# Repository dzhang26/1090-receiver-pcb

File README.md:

# 1090-receiver-pcb
PCB design for the 1.09 GHz mode-A/C/S / ADS-B receiver

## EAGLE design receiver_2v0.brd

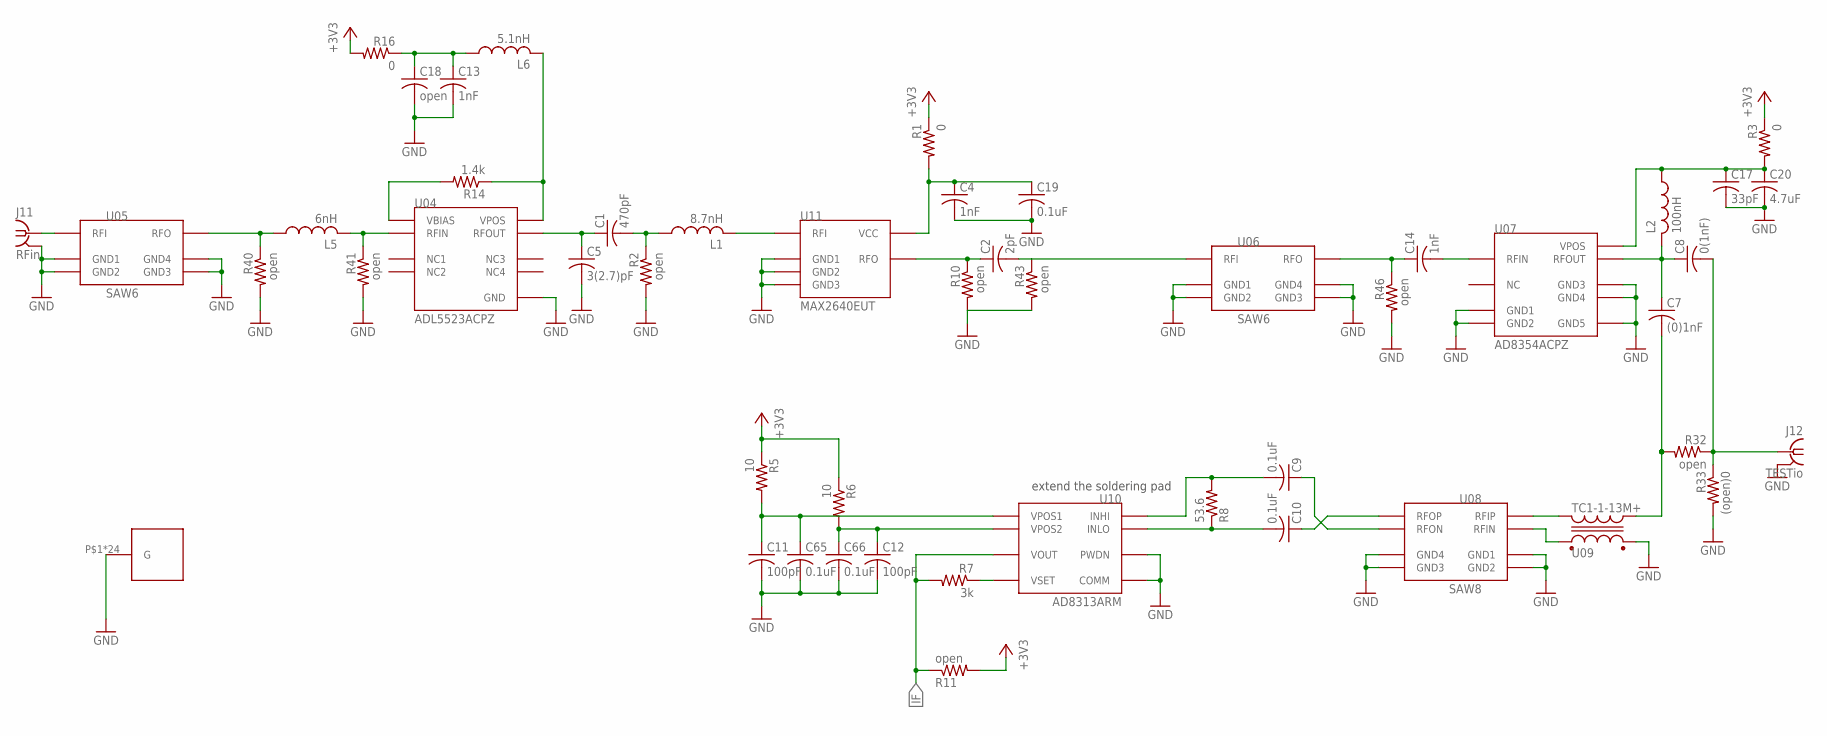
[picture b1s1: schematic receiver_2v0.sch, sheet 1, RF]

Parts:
C1: 470pF; C0603
C2: 2pF; C0603
C4, C13, C14: 1nF; C0603
C5: 3(2.7)pF; C0603
C7: (0)1nF; C0603
C8: 0(1nF); C0603
C9, C10, C19, C65, C66: 0.1uF; C0603
C11, C12: 100pF; C0603
C17: 33pF; C0603
C18: open; C0603
C20: 4.7uF; C0603
J11: RFin; J502-ND-142-0711-821/826; MPN 142-0711-821
J12: TESTio; J502-ND-142-0711-821/826; MPN 142-0711-821
L1: 8.7nH; L0603
L2: 100nH; L0603
L5: 6nH; L0603
L6: 5.1nH; L0603
R1, R3, R16: 0; R0603
R2, R10, R11, R32, R40, R41, R43, R46: open; R0603
R5, R6: 10; R0603
R7: 3k; R0603
R8: 53.6; R0603
R14: 1.4k; R0603
R33: (open)0; R0603
U04: ADL5523ACPZ; CP-8-2
U05, U06: SAW6
U07: AD8354ACPZ; CP-8-1
U08: SAW8
U09: TC1-1-13M+; AT224-1A
U10: AD8313ARM; RM-08
U11: MAX2640EUT; SOT23-6
U$8: BMI-S-5; BMI-S-105

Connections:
+3V3: R1.1, R3.1, R5.1, R6.1, R11.2, R16.2; also elsewhere on the board
GND: C4.2, C5.2, C11.2, C12.2, C13.2, C17.2, C18.2, C19.2, C20.2, C65.2, C66.2, J11.G@1 (GND), J11.G@2 (GND), J11.G@3 (GND), J11.G@4 (GND), J12.G@1 (GND), J12.G@2 (GND), J12.G@3 (GND), J12.G@4 (GND), R2.2, R10.2, R33.2, R40.2, R41.2, R43.2, R46.2, U04.9 (GND), U05.A (GND1), U05.C (GND2), U05.D (GND3), U05.F (GND4), U06.A (GND1), U06.C (GND2), U06.D (GND3), U06.F (GND4), U07.1 (GND1), U07.4 (GND2), U07.5 (GND3), U07.8 (GND4), U07.9 (GND5), U08.P3 (GND1), U08.P4 (GND2), U08.P7 (GND3), U08.P8 (GND4), U09.1 (SD), U10.5 (PWDN), U10.6 (COMM), U11.2 (GND1), U11.3 (GND2), U11.5 (GND3), U$8.P$1, U$8.P$2, U$8.P$3, U$8.P$4, U$8.P$5, U$8.P$6, U$8.P$7, U$8.P$8, U$8.P$9, U$8.P$10, U$8.P$11, U$8.P$12, U$8.P$13, U$8.P$15, U$8.P$16, U$8.P$17, U$8.P$18, U$8.P$20, U$8.P$21, U$8.P$22, U$8.P$23, U$8.P$24, U$8.P$25, U$8.P$26; also elsewhere on the board
IF: R7.2, R11.1, U10.8 (VOUT); also elsewhere on the board
unnamed: L1.2, U11.1 (RFI)
unnamed: C1.1, C5.1, U04.7 (RFOUT)
unnamed: C2.1, R10.1, U11.4 (RFO)
unnamed: C13.1, C18.1, L6.1, R16.1
unnamed: C14.2, U07.3 (RFIN)
unnamed: J11.1, U05.B (RFI)
unnamed: L6.2, R14.1, U04.8 (VPOS)
unnamed: C4.1, C19.1, R1.2, U11.6 (VCC)
unnamed: C17.1, C20.1, L2.1, R3.2, U07.6 (VPOS)
unnamed: C10.2, R8.1, U10.3 (INLO)
unnamed: C11.1, C65.1, R5.2, U10.1 (VPOS1)
unnamed: C12.1, C66.1, R6.2, U10.4 (VPOS2)
unnamed: C10.1, U08.P5 (RFOP)
unnamed: C9.1, U08.P6 (RFON)
unnamed: C9.2, R8.2, U10.2 (INHI)
unnamed: C7.1, C8.1, L2.2, U07.7 (RFOUT)
unnamed: C8.2, J12.1, R32.1, R33.1
unnamed: U08.P1 (RFIP), U09.4
unnamed: U08.P2 (RFIN), U09.6 (PD)
unnamed: C14.1, R46.1, U06.E (RFO)
unnamed: R14.2, U04.1 (VBIAS)
unnamed: L5.1, R40.1, U05.E (RFO)
unnamed: L5.2, R41.1, U04.2 (RFIN)
unnamed: R7.1, U10.7 (VSET)
unnamed: C1.2, L1.1, R2.1
unnamed: C2.2, R43.1, U06.B (RFI)
unnamed: C7.2, R32.2, U09.3 (S)

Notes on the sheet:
extend the soldering pad

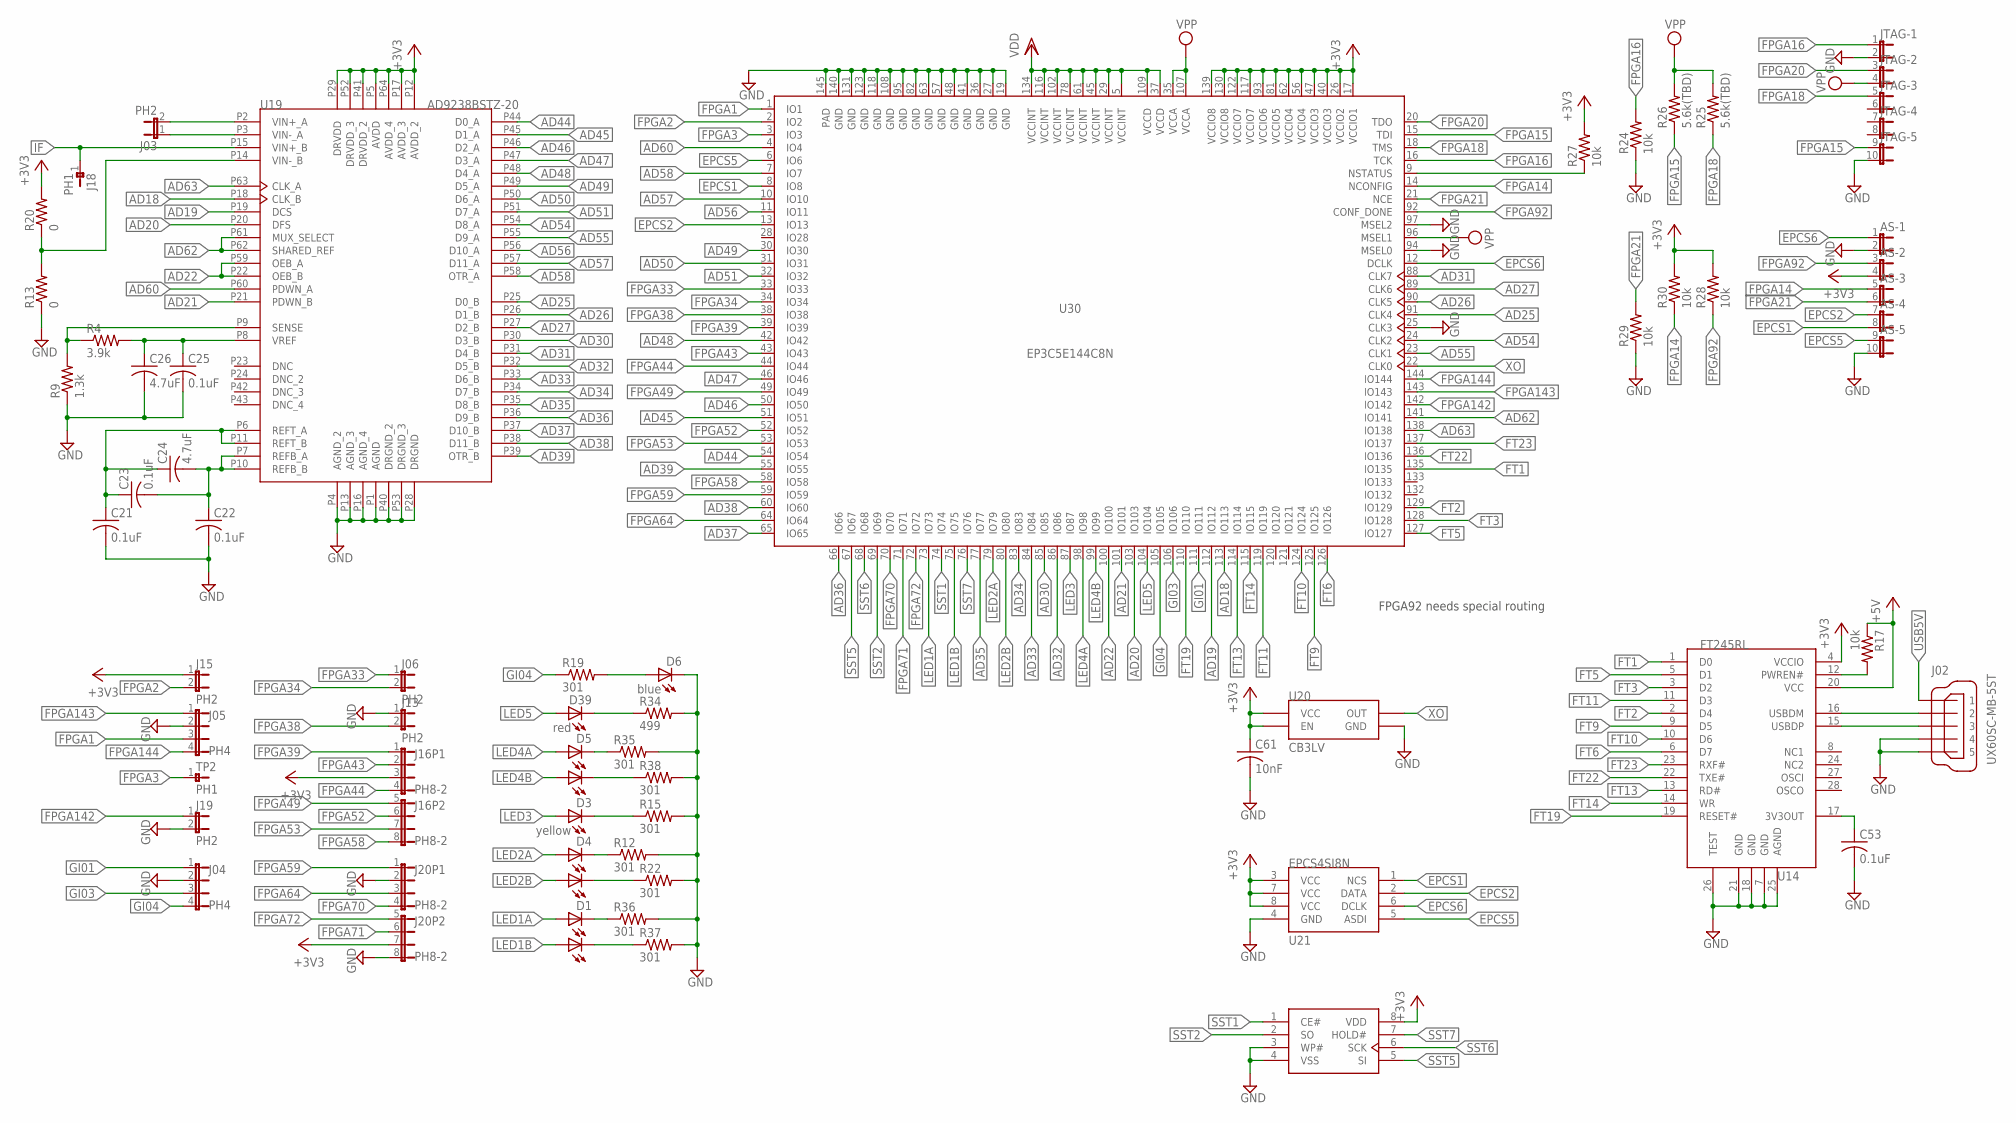
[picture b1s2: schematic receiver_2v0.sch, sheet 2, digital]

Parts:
AS: JP5QE; JP5Q
C21, C22, C23, C25, C53: 0.1uF; C0603
C24, C26: 4.7uF; C0603
C61: 10nF; C0603
D1, D4, D5: LED0606
D3: yellow; LED0603
D6: blue; LED0603
D39: red; LED0603
J02: UX60SC-MB-5ST
J03, J06, J13, J15, J19: PH2
J04, J05: PH4
J16, J20: PH8-2
J18: PH1
JTAG: JP5QE; JP5Q
R4: 3.9k; R0603
R9: 1.3k; R0603
R12, R15, R19, R22, R35, R36, R37, R38: 301; R0603
R13, R20: 0; R0603
R17, R24, R27, R28, R29, R30: 10k; R0603
R25, R26: 5.6k(TBD); R0603
R34: 499; R0603
TP2: PH1
U14: FT245RL; SSOP-28
U19: AD9238BSTZ-20; ST-64-1
U20: CB3LV; CB3
U21: EPCS4SI8N; SOIC-8
U23: SST25VF512A-33-4C-SAE; SOIC-8
U30: EP3C5E144C8N; EQFP144

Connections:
+3V3: AS.4 (2), C61.1, J15.1, J16.3, J20.7 (3), R20.2, R27.2, R28.2, R30.2, U14.4 (VCCIO), U19.P5 (AVDD), U19.P12 (AVDD_2), U19.P17 (AVDD_3), U19.P29 (DRVDD), U19.P41 (DRVDD_2), U19.P52 (DRVDD_3), U19.P64 (AVDD_4), U20.1 (EN), U20.4 (VCC), U21.3 (VCC), U21.7 (VCC), U21.8 (VCC), U23.8 (VDD), U30.17 (VCCIO1), U30.26 (VCCIO2), U30.40 (VCCIO3), U30.47 (VCCIO3), U30.56 (VCCIO4), U30.62 (VCCIO4), U30.81 (VCCIO5), U30.93 (VCCIO6), U30.117 (VCCIO7), U30.122 (VCCIO7), U30.130 (VCCIO8), U30.139 (VCCIO8); also elsewhere on the board
+5V: R17.1, U14.20 (VCC); also elsewhere on the board
AD18: U19.P18 (CLK_B), U30.113 (IO113)
AD19: U19.P19 (DCS), U30.112 (IO112)
AD20: U19.P20 (DFS), U30.103 (IO103)
AD21: U19.P21 (PDWN_B), U30.101 (IO101)
AD22: U19.P22 (OEB_B), U19.P59 (OEB_A), U30.100 (IO100)
AD25: U19.P25 (D0_B), U30.91 (CLK4)
AD26: U19.P26 (D1_B), U30.90 (CLK5)
AD27: U19.P27 (D2_B), U30.89 (CLK6)
AD30: U19.P30 (D3_B), U30.85 (IO85)
AD31: U19.P31 (D4_B), U30.88 (CLK7)
AD32: U19.P32 (D5_B), U30.86 (IO86)
AD33: U19.P33 (D6_B), U30.84 (IO84)
AD34: U19.P34 (D7_B), U30.83 (IO83)
AD35: U19.P35 (D8_B), U30.77 (IO77)
AD36: U19.P36 (D9_B), U30.66 (IO66)
AD37: U19.P37 (D10_B), U30.65 (IO65)
AD38: U19.P38 (D11_B), U30.60 (IO60)
AD39: U19.P39 (OTR_B), U30.55 (IO55)
AD44: U19.P44 (D0_A), U30.54 (IO54)
AD45: U19.P45 (D1_A), U30.51 (IO51)
AD46: U19.P46 (D2_A), U30.50 (IO50)
AD47: U19.P47 (D3_A), U30.46 (IO46)
AD48: U19.P48 (D4_A), U30.42 (IO42)
AD49: U19.P49 (D5_A), U30.30 (IO30)
AD50: U19.P50 (D6_A), U30.31 (IO31)
AD51: U19.P51 (D7_A), U30.32 (IO32)
AD54: U19.P54 (D8_A), U30.24 (CLK2)
AD55: U19.P55 (D9_A), U30.23 (CLK1)
AD56: U19.P56 (D10_A), U30.11 (IO11)
AD57: U19.P57 (D11_A), U30.10 (IO10)
AD58: U19.P58 (OTR_A), U30.7 (IO7)
AD60: U19.P60 (PDWN_A), U30.4 (IO4)
AD62: U19.P61 (MUX_SELECT), U19.P62 (SHARED_REF), U30.141 (IO141)
AD63: U19.P63 (CLK_A), U30.138 (IO138)
ADREFB: C22.1, C23.2, C24.2, U19.P7 (REFB_A), U19.P10 (REFB_B)
ADREFY: C21.1, C23.1, C24.1, U19.P6 (REFT_A), U19.P11 (REFT_B)
ADSENSE: R4.1, R9.2, U19.P9 (SENSE)
ADVINMA: J03.1, U19.P3 (VIN-_A)
ADVINMB: R13.2, R20.1, U19.P14 (VIN-_B)
ADVINPA: J03.2, U19.P2 (VIN+_A)
ADVREF: C25.1, C26.1, R4.2, U19.P8 (VREF)
EPCS1: AS.8 (2), U21.1 (NCS), U30.8 (IO8)
EPCS2: AS.7 (1), U21.2 (DATA), U30.13 (IO13)
EPCS5: AS.9 (1), U21.5 (ASDI), U30.6 (IO6)
EPCS6: AS.1, U21.6 (DCLK), U30.12 (DCLK)
FPGA1: J05.3, U30.1 (IO1)
FPGA2: J15.2, U30.2 (IO2)
FPGA3: TP2.1, U30.3 (IO3)
FPGA9: R27.1, U30.9 (NSTATUS)
FPGA14: AS.5 (1), R30.1, U30.14 (NCONFIG)
FPGA15: JTAG.9 (1), R26.1, U30.15 (TDI)
FPGA16: JTAG.1, R24.2, U30.16 (TCK)
FPGA18: JTAG.5 (1), R25.1, U30.18 (TMS)
FPGA20: JTAG.3 (1), U30.20 (TDO)
FPGA21: AS.6 (2), R29.2, U30.21 (NCE)
FPGA33: J06.1, U30.33 (IO33)
FPGA34: J06.2, U30.34 (IO34)
FPGA38: J13.2, U30.38 (IO38)
FPGA39: J16.1, U30.39 (IO39)
FPGA43: J16.2, U30.43 (IO43)
FPGA44: J16.4, U30.44 (IO44)
FPGA49: J16.5 (1), U30.49 (IO49)
FPGA52: J16.6 (2), U30.52 (IO52)
FPGA53: J16.7 (3), U30.53 (IO53)
FPGA58: J16.8 (4), U30.58 (IO58)
FPGA59: J20.1, U30.59 (IO59)
FPGA64: J20.3, U30.64 (IO64)
FPGA70: J20.4, U30.70 (IO70)
FPGA71: J20.6 (2), U30.71 (IO71)
FPGA72: J20.5 (1), U30.72 (IO72)
FPGA92: AS.3 (1), R28.1, U30.92 (CONF_DONE)
FPGA142: J19.1, U30.142 (IO142)
FPGA143: J05.1, U30.143 (IO143)
FPGA144: J05.4, U30.144 (IO144)
FT1: U14.1 (D0), U30.135 (IO135)
FT2: U14.2 (D4), U30.129 (IO129)
FT3: U14.3 (D2), U30.128 (IO128)
FT5: U14.5 (D1), U30.127 (IO127)
FT6: U14.6 (D7), U30.126 (IO126)
FT9: U14.9 (D5), U30.125 (IO125)
FT10: U14.10 (D6), U30.124 (IO124)
FT11: U14.11 (D3), U30.119 (IO119)
FT12: R17.2, U14.12 (PWREN#)
FT13: U14.13 (RD#), U30.114 (IO114)
FT14: U14.14 (WR), U30.115 (IO115)
FT19: U14.19 (RESET#), U30.110 (IO110)
FT22: U14.22 (TXE#), U30.136 (IO136)
FT23: U14.23 (RXF#), U30.137 (IO137)
GI01: J04.1, U30.111 (IO111)
GI03: J04.3, U30.106 (IO106)
GI04: J04.4, R19.1, U30.105 (IO105)
GND: AS.2, AS.10 (2), C21.2, C22.2, C25.2, C26.2, C53.2, C61.2, D6.C, J02.4, J02.5, J04.2, J05.2, J13.1, J19.2, J20.2, J20.8 (4), JTAG.2, JTAG.10 (2), R9.1, R12.2, R13.1, R15.2, R22.2, R24.1, R29.1, R34.2, R35.2, R36.2, R37.2, R38.2, U14.7 (GND), U14.18 (GND), U14.21 (GND), U14.25 (AGND), U14.26 (TEST), U19.P1 (AGND), U19.P4 (AGND_2), U19.P13 (AGND_3), U19.P16 (AGND_4), U19.P28 (DRGND), U19.P40 (DRGND_2), U19.P53 (DRGND_3), U20.2 (GND), U21.4 (GND), U23.3 (WP#), U23.4 (VSS), U30.19 (GND), U30.25 (CLK3), U30.27 (GND), U30.36 (GND), U30.41 (GND), U30.48 (GND), U30.57 (GND), U30.63 (GND), U30.82 (GND), U30.94 (MSEL0), U30.95 (GND), U30.97 (MSEL2), U30.108 (GND), U30.118 (GND), U30.123 (GND), U30.131 (GND), U30.140 (GND), U30.145 (PAD); also elsewhere on the board
IF: J18.1, U19.P15 (VIN+_B); also elsewhere on the board
LED1A: D1.A1, U30.73 (IO73)
LED1B: D1.A0, U30.75 (IO75)
LED2A: D4.A1, U30.79 (IO79)
LED2B: D4.A0, U30.80 (IO80)
LED3: D3.A, U30.87 (IO87)
LED4A: D5.A1, U30.98 (IO98)
LED4B: D5.A0, U30.99 (IO99)
LED5: D39.A, U30.104 (IO104)
unnamed: C53.1, U14.17 (3V3OUT)
unnamed: D4.C1, R12.1
unnamed: D39.C, R34.1
unnamed: D6.A, R19.2
unnamed: D3.C, R15.1
unnamed: D1.C1, R36.1
unnamed: D4.C0, R22.1
unnamed: D5.C1, R35.1
unnamed: D1.C0, R37.1
unnamed: D5.C0, R38.1
SST1: U23.1 (CE#), U30.74 (IO74)
SST2: U23.2 (SO), U30.69 (IO69)
SST5: U23.5 (SI), U30.67 (IO67)
SST6: U23.6 (SCK), U30.68 (IO68)
SST7: U23.7 (HOLD#), U30.76 (IO76)
USB5V: J02.1; also elsewhere on the board
USBDM: J02.2, U14.16 (USBDM)
USBDP: J02.3, U14.15 (USBDP)
VDD: U30.5 (VCCINT), U30.29 (VCCINT), U30.37 (VCCD), U30.45 (VCCINT), U30.61 (VCCINT), U30.78 (VCCINT), U30.102 (VCCINT), U30.109 (VCCD), U30.116 (VCCINT), U30.134 (VCCINT); also elsewhere on the board
VPP: JTAG.4 (2), R25.2, R26.2, U30.35 (VCCA), U30.96 (MSEL1), U30.107 (VCCA); also elsewhere on the board
XO: U20.3 (OUT), U30.22 (CLK0)

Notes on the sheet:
FPGA92 needs special routing

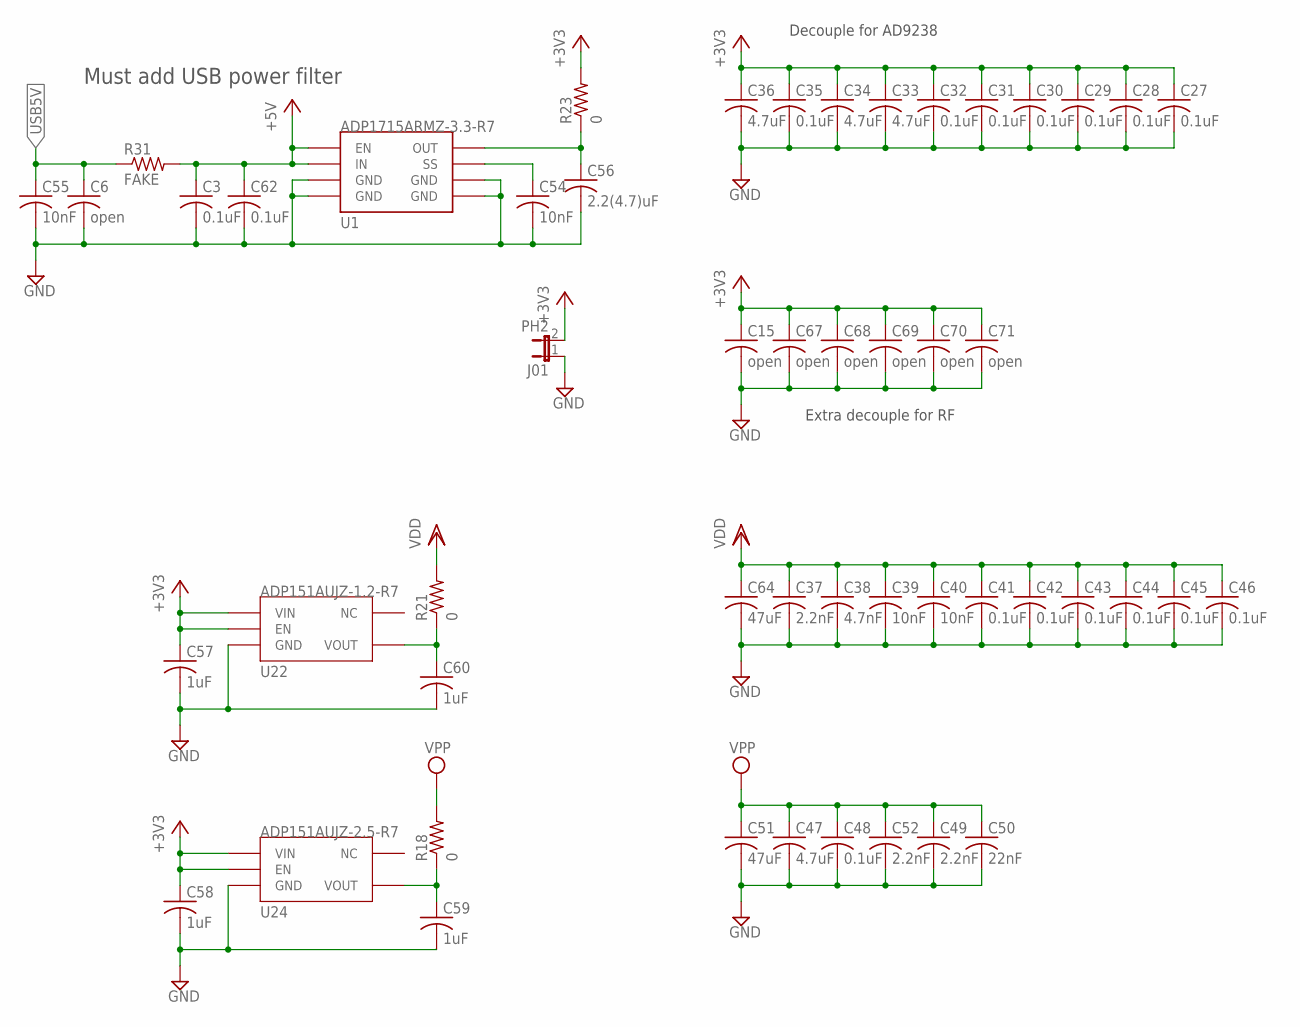
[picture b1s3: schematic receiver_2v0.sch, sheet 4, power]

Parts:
C3, C27, C28, C29, C30, C31, C32, C35, C41, C42, C43, C44, C45, C46, C48, C62: 0.1uF; C0603
C6, C15, C67, C68, C69, C70, C71: open; C0603
C33, C34, C36, C47: 4.7uF; C0603
C37, C49, C52: 2.2nF; C0603
C38: 4.7nF; C0603
C39, C40, C54, C55: 10nF; C0603
C50: 22nF; C0603
C51, C64: 47uF; C1206
C56: 2.2(4.7)uF; C0603
C57, C58, C59, C60: 1uF; C0603
J01: PH2
R18, R21, R23: 0; R0603
R31: FAKE; R0603
U1: ADP1715ARMZ-3.3-R7; RM-08
U22: ADP151AUJZ-1.2-R7; UJ-5
U24: ADP151AUJZ-2.5-R7; UJ-5

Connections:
+3V3: C15.1, C27.1, C28.1, C29.1, C30.1, C31.1, C32.1, C33.1, C34.1, C35.1, C36.1, C57.1, C58.1, C67.1, C68.1, C69.1, C70.1, C71.1, J01.2, R23.2, U22.1 (VIN), U22.3 (EN), U24.1 (VIN), U24.3 (EN); also elsewhere on the board
+5V: C3.1, C62.1, R31.2, U1.1 (EN), U1.2 (IN); also elsewhere on the board
ADP1715_3: C56.1, R23.1, U1.3 (OUT)
GND: C3.2, C6.2, C15.2, C27.2, C28.2, C29.2, C30.2, C31.2, C32.2, C33.2, C34.2, C35.2, C36.2, C37.2, C38.2, C39.2, C40.2, C41.2, C42.2, C43.2, C44.2, C45.2, C46.2, C47.2, C48.2, C49.2, C50.2, C51.2, C52.2, C54.2, C55.2, C56.2, C57.2, C58.2, C59.2, C60.2, C62.2, C64.2, C67.2, C68.2, C69.2, C70.2, C71.2, J01.1, U1.5 (GND), U1.6 (GND), U1.7 (GND), U1.8 (GND), U22.2 (GND), U24.2 (GND); also elsewhere on the board
unnamed: C60.1, R21.1, U22.5 (VOUT)
unnamed: C59.1, R18.1, U24.5 (VOUT)
unnamed: C54.1, U1.4 (SS)
USB5V: C6.1, C55.1, R31.1; also elsewhere on the board
VDD: C37.1, C38.1, C39.1, C40.1, C41.1, C42.1, C43.1, C44.1, C45.1, C46.1, C64.1, R21.2; also elsewhere on the board
VPP: C47.1, C48.1, C49.1, C50.1, C51.1, C52.1, R18.2; also elsewhere on the board

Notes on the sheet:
Decouple for AD9238
Extra decouple for RF
Must add USB power filter

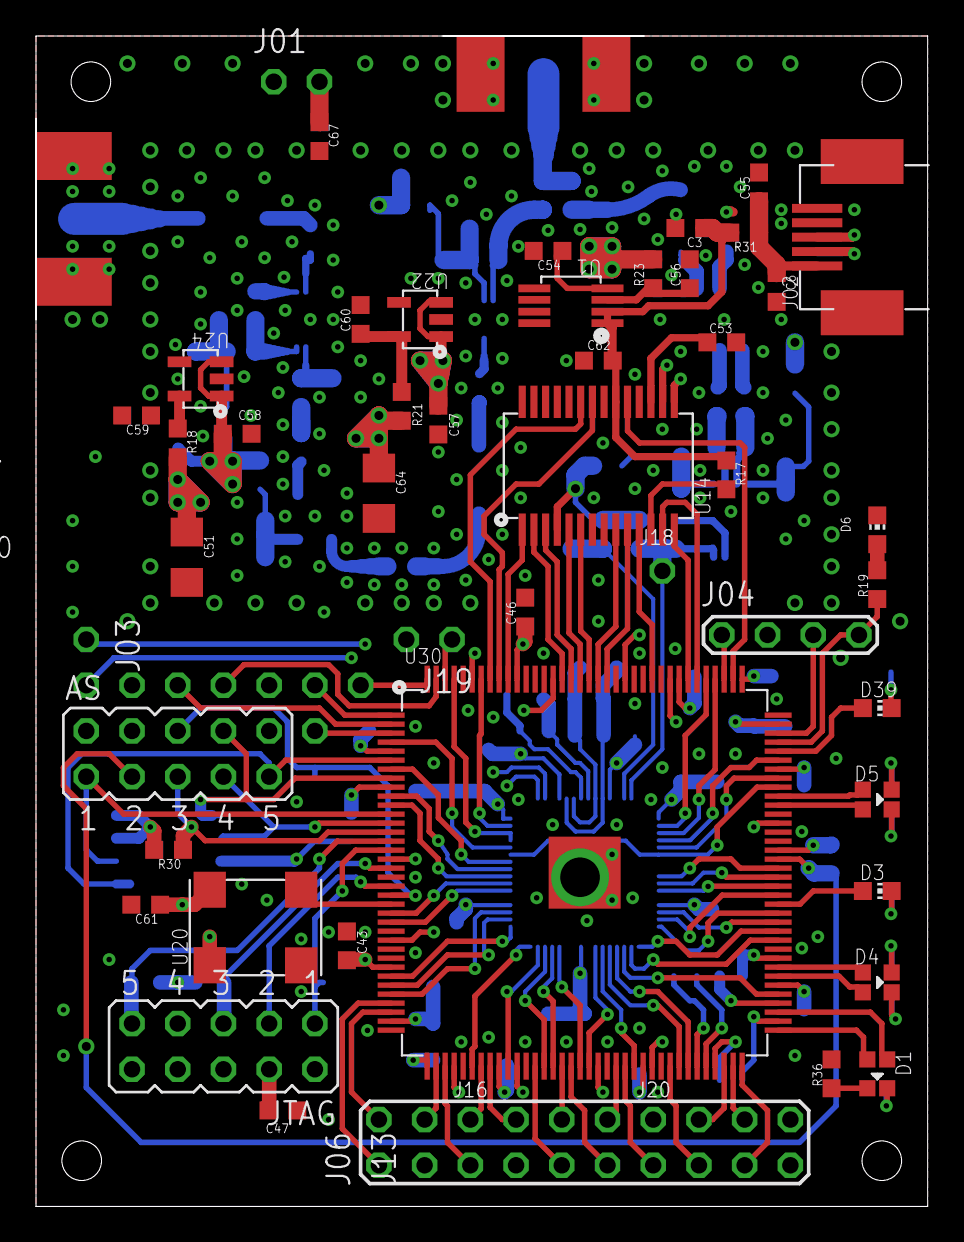
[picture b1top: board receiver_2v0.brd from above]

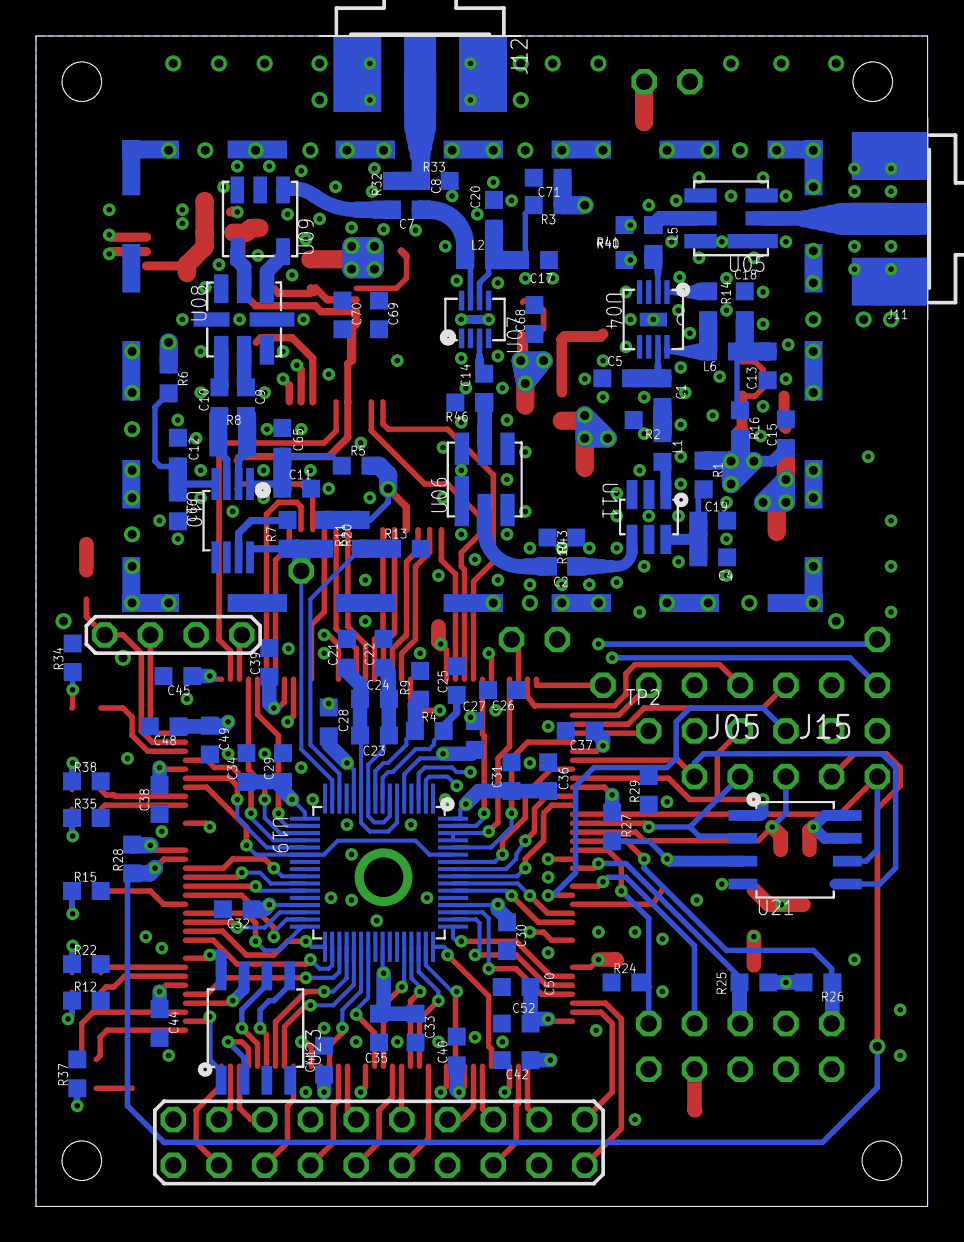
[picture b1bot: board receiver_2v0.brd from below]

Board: 4 copper layers, 49.5 x 65.0 mm, 156 parts (106 on the bottom side), 155 nets.

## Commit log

2015-05-06 Draft version
    Version 2.0
2015-05-07 Draft version
    Reorganized schematic, no air wire in the layout
2015-05-07 Draft version
    Added an ignore file
2015-05-07 Draft version
    Removed all temp files

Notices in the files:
receiver_2v0.brd:
All Rights Reserved
